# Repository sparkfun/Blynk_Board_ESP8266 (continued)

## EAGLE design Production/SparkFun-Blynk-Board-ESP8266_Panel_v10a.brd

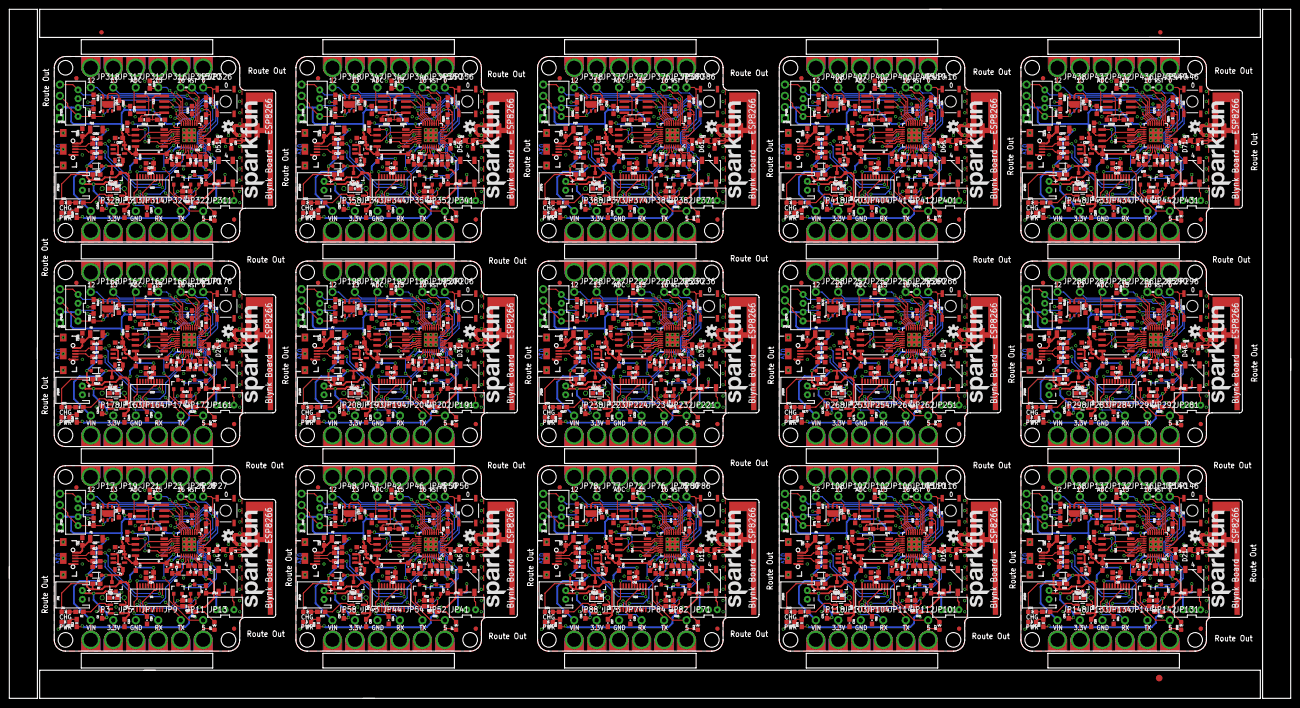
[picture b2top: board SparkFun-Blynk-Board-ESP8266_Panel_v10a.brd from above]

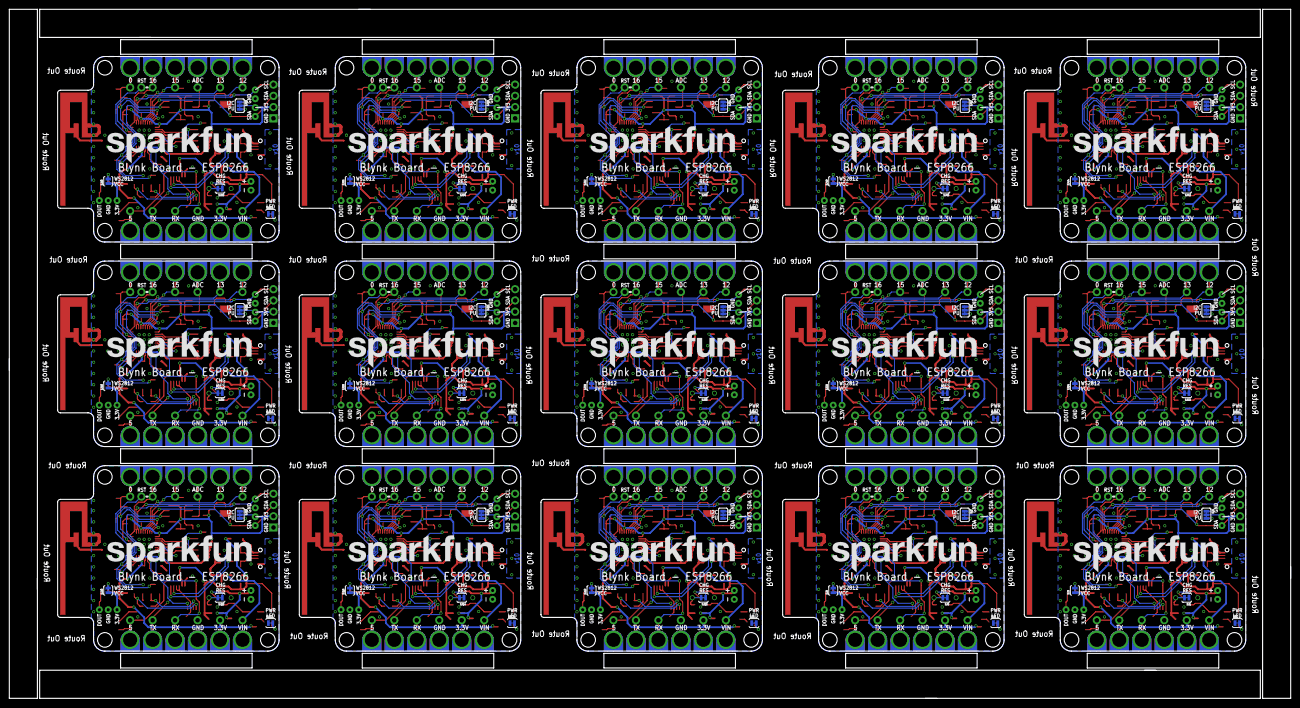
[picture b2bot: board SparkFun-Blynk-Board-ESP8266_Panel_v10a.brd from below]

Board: 2 copper layers, 289.6 x 155.7 mm, 1548 parts (75 on the bottom side), 840 nets.

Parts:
C1, C20, C39, C58, C77, C96, C115, C134, C153, C172, C191, C210, C229, C248, C267: 10uF; 0603-CAP
C2, C5, C9, C11, C14, C16, C17, C18, C21, C23, C24, C25, C29, C32, C33, C34, C40, C42, C43, C44, C48, C51, C52, C53, C59, C61, C62, C63, C67, C70, C71, C72, C78, C80, C81, C82, C86, C89, C90, C91, C97, C99, C100, C101, C105, C108, C109, C110, C116, C118, C119, C120, C124, C127, C128, C129, C135, C137, C138, C139, C143, C146, C147, C148, C154, C156, C157, C158, C162, C165, C166, C167, C173, C175, C176, C177, C181, C184, C185, C186, C192, C194, C195, C196, C200, C203, C204, C205, C211, C213, C214, C215, C219, C222, C223, C224, C230, C232, C233, C234, C238, C241, C242, C243, C249, C251, C252, C253, C257, C260, C261, C262, C268, C270, C271, C272, C276, C279, C280, C281: 0.1uF; 0603-CAP
C3, C4, C26, C27, C45, C46, C64, C65, C83, C84, C102, C103, C121, C122, C140, C141, C159, C160, C178, C179, C197, C198, C216, C217, C235, C236, C254, C255, C273, C274: 10pF; 0603-CAP
C6, C15, C19, C31, C37, C38, C50, C56, C57, C69, C75, C76, C88, C94, C95, C107, C113, C114, C126, C132, C133, C145, C151, C152, C164, C170, C171, C183, C189, C190, C202, C208, C209, C221, C227, C228, C240, C246, C247, C259, C265, C266, C278, C284, C285: 4.7uF; 0603-CAP
C7, C35, C54, C73, C92, C111, C130, C149, C168, C187, C206, C225, C244, C263, C282: 1.0uF; 0805-CAP
C8, C28, C47, C66, C85, C104, C123, C142, C161, C180, C199, C218, C237, C256, C275: 5.6pF; 0603-CAP
C10, C36, C55, C74, C93, C112, C131, C150, C169, C188, C207, C226, C245, C264, C283: 2.2uF; 0603-CAP
C12, C13, C22, C30, C41, C49, C60, C68, C79, C87, C98, C106, C117, C125, C136, C144, C155, C163, C174, C182, C193, C201, C212, C220, C231, C239, C250, C258, C269, C277: 47pF; 0603-CAP
D1, D9, D14, D19, D24, D29, D34, D39, D44, D49, D54, D59, D64, D69, D74: Yellow; LED-0603
D2, D8, D13, D18, D23, D28, D33, D38, D43, D48, D53, D58, D63, D68, D73: BAT20J; SOD-323
D3, D7, D12, D17, D22, D27, D32, D37, D42, D47, D52, D57, D62, D67, D72: BLUE; LED-0603
D4, D6, D11, D16, D21, D26, D31, D36, D41, D46, D51, D56, D61, D66, D71: WS2812; WS2812B
D5, D10, D15, D20, D25, D30, D35, D40, D45, D50, D55, D60, D65, D70, D75: RED; LED-0603
E1, E2, E3, E4, E5, E6, E7, E8, E9, E10, E11, E12, E13, E14, E15: ANTENNATRACE; TRACE_ANTENNA_2.4GHZ_25.7MM
E$1: FIDUCIAL-1.5X3
E$7, E$8: FIDUCIAL-1X2
F1, F2, F3, F4, F5, F6, F7, F8, F9, F10, F11, F12, F13, F14, F15: 500mA; PTC-1206
FID1, FID2, FID3, FID4, FID5, FID6, FID7, FID8, FID9, FID10, FID11, FID12, FID13, FID14, FID15, FID16, FID17, FID18, FID19, FID20, FID21, FID22, FID23, FID24, FID25, FID26, FID27, FID28, FID29, FID30: FIDUCIAL1X2; FIDUCIAL-1X2
IC1, IC2, IC3, IC4, IC5, IC6, IC7, IC8, IC9, IC10, IC11, IC12, IC13, IC14, IC15: LMV358; SO08
JP1, JP49, JP79, JP109, JP139, JP169, JP199, JP229, JP259, JP289, JP319, JP349, JP379, JP409, JP439: LiPo; JST-2-PTH
JP2, JP4, JP6, JP8, JP10, JP12, JP16, JP18, JP20, JP22, JP24, JP26, JP32, JP33, JP34, JP35, JP36, JP37, JP38, JP39, JP51, JP53, JP55, JP57, JP62, JP63, JP64, JP65, JP66, JP67, JP68, JP69, JP81, JP83, JP85, JP87, JP92, JP93, JP94, JP95, JP96, JP97, JP98, JP99, JP111, JP113, JP115, JP117, JP122, JP123, JP124, JP125, JP126, JP127, JP128, JP129, JP141, JP143, JP145, JP147, JP152, JP153, JP154, JP155, JP156, JP157, JP158, JP159, JP171, JP173, JP175, JP177, JP182, JP183, JP184, JP185, JP186, JP187, JP188, JP189, JP201, JP203, JP205, JP207, JP212, JP213, JP214, JP215, JP216, JP217, JP218, JP219, JP231, JP233, JP235, JP237, JP242, JP243, JP244, JP245, JP246, JP247, JP248, JP249, JP261, JP263, JP265, JP267, JP272, JP273, JP274, JP275, JP276, JP277, JP278, JP279, JP291, JP293, JP295, JP297, JP302, JP303, JP304, JP305, JP306, JP307, JP308, JP309, JP321, JP323, JP325, JP327, JP332, JP333, JP334, JP335, JP336, JP337, JP338, JP339, JP351, JP353, JP355, JP357, JP362, JP363, JP364, JP365, JP366, JP367, JP368, JP369, JP381, JP383, JP385, JP387, JP392, JP393, JP394, JP395, JP396, JP397, JP398, JP399, JP411, JP413, JP415, JP417, JP422, JP423, JP424, JP425, JP426, JP427, JP428, JP429, JP441, JP443, JP445, JP447: 1X01_ALLIGATOR_3MM_HALF
JP3, JP5, JP7, JP9, JP11, JP13, JP17, JP19, JP21, JP23, JP25, JP27, JP28, JP41, JP42, JP43, JP44, JP45, JP46, JP47, JP48, JP50, JP52, JP54, JP56, JP58, JP71, JP72, JP73, JP74, JP75, JP76, JP77, JP78, JP80, JP82, JP84, JP86, JP88, JP101, JP102, JP103, JP104, JP105, JP106, JP107, JP108, JP110, JP112, JP114, JP116, JP118, JP131, JP132, JP133, JP134, JP135, JP136, JP137, JP138, JP140, JP142, JP144, JP146, JP148, JP161, JP162, JP163, JP164, JP165, JP166, JP167, JP168, JP170, JP172, JP174, JP176, JP178, JP191, JP192, JP193, JP194, JP195, JP196, JP197, JP198, JP200, JP202, JP204, JP206, JP208, JP221, JP222, JP223, JP224, JP225, JP226, JP227, JP228, JP230, JP232, JP234, JP236, JP238, JP251, JP252, JP253, JP254, JP255, JP256, JP257, JP258, JP260, JP262, JP264, JP266, JP268, JP281, JP282, JP283, JP284, JP285, JP286, JP287, JP288, JP290, JP292, JP294, JP296, JP298, JP311, JP312, JP313, JP314, JP315, JP316, JP317, JP318, JP320, JP322, JP324, JP326, JP328, JP341, JP342, JP343, JP344, JP345, JP346, JP347, JP348, JP350, JP352, JP354, JP356, JP358, JP371, JP372, JP373, JP374, JP375, JP376, JP377, JP378, JP380, JP382, JP384, JP386, JP388, JP401, JP402, JP403, JP404, JP405, JP406, JP407, JP408, JP410, JP412, JP414, JP416, JP418, JP431, JP432, JP433, JP434, JP435, JP436, JP437, JP438, JP440, JP442, JP444, JP446, JP448: 1X01_NO_SILK
JP14, JP40, JP70, JP100, JP130, JP160, JP190, JP220, JP250, JP280, JP310, JP340, JP370, JP400, JP430: JST-3-PTH-VERT
JP15, JP31, JP61, JP91, JP121, JP151, JP181, JP211, JP241, JP271, JP301, JP331, JP361, JP391, JP421: USB-B-MICRO-SMD_V03
JP29, JP60, JP90, JP120, JP150, JP180, JP210, JP240, JP270, JP300, JP330, JP360, JP390, JP420, JP450: JST-4-PTH-VERT
JP30, JP59, JP89, JP119, JP149, JP179, JP209, JP239, JP269, JP299, JP329, JP359, JP389, JP419, JP449: 1X04_NO_SILK
L1, L2, L3, L4, L5, L6, L7, L8, L9, L10, L11, L12, L13, L14, L15, L16, L17, L18, L19, L20, L21, L22, L23, L24, L25, L26, L27, L28, L29, L30: DNP; 0603
LOGO1, LOGO4, LOGO7, LOGO10, LOGO13, LOGO16, LOGO19, LOGO22, LOGO25, LOGO28, LOGO31, LOGO34, LOGO37, LOGO40, LOGO43: SFE_LOGO_NAME.2_INCH; SFE_LOGO_NAME_.2
LOGO2, LOGO5, LOGO8, LOGO11, LOGO14, LOGO17, LOGO20, LOGO23, LOGO26, LOGO29, LOGO32, LOGO35, LOGO38, LOGO41, LOGO44: OSHW-LOGOS; OSHW-LOGO-S
LOGO3, LOGO6, LOGO9, LOGO12, LOGO15, LOGO18, LOGO21, LOGO24, LOGO27, LOGO30, LOGO33, LOGO36, LOGO39, LOGO42, LOGO45: SFE_LOGO_NAME.3_INCH; SFE_LOGO_NAME_.3
Q1, Q6, Q9, Q12, Q15, Q18, Q21, Q24, Q27, Q30, Q33, Q36, Q39, Q42, Q45: 2.5A/30V; SOT23-3
Q2, Q3, Q4, Q5, Q7, Q8, Q10, Q11, Q13, Q14, Q16, Q17, Q19, Q20, Q22, Q23, Q25, Q26, Q28, Q29, Q31, Q32, Q34, Q35, Q37, Q38, Q40, Q41, Q43, Q44: MMBT2222A; SOT23-3@1
R1, R21, R41, R61, R81, R101, R121, R141, R161, R181, R201, R221, R241, R261, R281: 12k; 0603-RES
R2, R12, R37, R38, R57, R58, R77, R78, R97, R98, R117, R118, R137, R138, R157, R158, R177, R178, R197, R198, R217, R218, R237, R238, R257, R258, R277, R278, R297, R298: 1K; 0603-RES
R3, R33, R53, R73, R93, R113, R133, R153, R173, R193, R213, R233, R253, R273, R293: 22K; 0603-RES
R4, R34, R54, R74, R94, R114, R134, R154, R174, R194, R214, R234, R254, R274, R294: 10K; 0603-RES
R5, R40, R60, R80, R100, R120, R140, R160, R180, R200, R220, R240, R260, R280, R300: DNP; 1/6W-RES
R6, R39, R59, R79, R99, R119, R139, R159, R179, R199, R219, R239, R259, R279, R299: 2.0k; 0603-RES
R7, R8, R10, R17, R18, R19, R20, R22, R23, R24, R25, R27, R30, R36, R42, R43, R44, R45, R47, R50, R56, R62, R63, R64, R65, R67, R70, R76, R82, R83, R84, R85, R87, R90, R96, R102, R103, R104, R105, R107, R110, R116, R122, R123, R124, R125, R127, R130, R136, R142, R143, R144, R145, R147, R150, R156, R162, R163, R164, R165, R167, R170, R176, R182, R183, R184, R185, R187, R190, R196, R202, R203, R204, R205, R207, R210, R216, R222, R223, R224, R225, R227, R230, R236, R242, R243, R244, R245, R247, R250, R256, R262, R263, R264, R265, R267, R270, R276, R282, R283, R284, R285, R287, R290, R296: 10K; 0603-RES@1
R9, R26, R46, R66, R86, R106, R126, R146, R166, R186, R206, R226, R246, R266, R286: 200; 0603-RES
R11, R35, R55, R75, R95, R115, R135, R155, R175, R195, R215, R235, R255, R275, R295: 330; 0603-RES
R13, R14, R28, R29, R48, R49, R68, R69, R88, R89, R108, R109, R128, R129, R148, R149, R168, R169, R188, R189, R208, R209, R228, R229, R248, R249, R268, R269, R288, R289: 27; 0603-RES
R15, R16, R31, R32, R51, R52, R71, R72, R91, R92, R111, R112, R131, R132, R151, R152, R171, R172, R191, R192, R211, R212, R231, R232, R251, R252, R271, R272, R291, R292: 4.7K; 0603-RES
S1, S2, S3, S4, S5, S6, S7, S8, S9, S10, S11, S12, S13, S14, S15: TACTILE-SWITCH-SMD
SJ1, SJ6, SJ10, SJ14, SJ18, SJ22, SJ26, SJ30, SJ34, SJ38, SJ42, SJ46, SJ50, SJ54, SJ58: PAD-JUMPER-2-NC_BY_TRACE_YES_SILK
SJ2, SJ5, SJ9, SJ13, SJ17, SJ21, SJ25, SJ29, SJ33, SJ37, SJ41, SJ45, SJ49, SJ53, SJ57: PWRLED; PAD-JUMPER-2-NC_BY_TRACE_YES_SILK
SJ3, SJ8, SJ12, SJ16, SJ20, SJ24, SJ28, SJ32, SJ36, SJ40, SJ44, SJ48, SJ52, SJ56, SJ60: WS2812-VCC; PAD-JUMPER-2-NC_BY_TRACE_YES_SILK
SJ4, SJ7, SJ11, SJ15, SJ19, SJ23, SJ27, SJ31, SJ35, SJ39, SJ43, SJ47, SJ51, SJ55, SJ59: PAD-JUMPER-3-3OF3_NC_BY_TRACE_YES_SILK_FULL_BOX
STANDOFF1, STANDOFF2, STANDOFF3, STANDOFF4, STANDOFF5, STANDOFF6, STANDOFF7, STANDOFF8, STANDOFF9, STANDOFF10, STANDOFF11, STANDOFF12, STANDOFF13, STANDOFF14, STANDOFF15, STANDOFF16, STANDOFF17, STANDOFF18, STANDOFF19, STANDOFF20, STANDOFF21, STANDOFF22, STANDOFF23, STANDOFF24, STANDOFF25, STANDOFF26, STANDOFF27, STANDOFF28, STANDOFF29, STANDOFF30, STANDOFF31, STANDOFF32, STANDOFF33, STANDOFF34, STANDOFF35, STANDOFF36, STANDOFF37, STANDOFF38, STANDOFF39, STANDOFF40, STANDOFF41, STANDOFF42, STANDOFF43, STANDOFF44, STANDOFF45, STANDOFF46, STANDOFF47, STANDOFF48, STANDOFF49, STANDOFF50, STANDOFF51, STANDOFF52, STANDOFF53, STANDOFF54, STANDOFF55, STANDOFF56, STANDOFF57, STANDOFF58, STANDOFF59, STANDOFF60: STAND-OFF
U1, U11, U17, U23, U29, U35, U41, U47, U53, U59, U65, U71, U77, U83, U89: MCP73831; SOT23-5
U2, U7, U13, U19, U25, U31, U37, U43, U49, U55, U61, U67, U73, U79, U85: ESP8266; QFN32
U3, U12, U18, U24, U30, U36, U42, U48, U54, U60, U66, U72, U78, U84, U90: AP2112K-3.3V; SOT23-5
U4, U9, U15, U21, U27, U33, U39, U45, U51, U57, U63, U69, U75, U81, U87: FT231XS-U; SSOP20_L
U5, U8, U14, U20, U26, U32, U38, U44, U50, U56, U62, U68, U74, U80, U86: W25Q32FVSS; SOIC-8
U6, U10, U16, U22, U28, U34, U40, U46, U52, U58, U64, U70, U76, U82, U88: SI7021
Y1, Y2, Y3, Y4, Y5, Y6, Y7, Y8, Y9, Y10, Y11, Y12, Y13, Y14, Y15: 26MHz; CRYSTAL-SMD-3.2X2.5

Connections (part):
0/BUTTON: JP26.1@2, JP27.1, Q3.3, R19.1, S1.1, S1.2, U2.15
0/BUTTON1: JP55.1@2, JP56.1, Q5.3, R23.1, S2.1, S2.2, U7.15
0/BUTTON2: JP85.1@2, JP86.1, Q8.3, R43.1, S3.1, S3.2, U13.15
0/BUTTON3: JP115.1@2, JP116.1, Q11.3, R63.1, S4.1, S4.2, U19.15
0/BUTTON4: JP145.1@2, JP146.1, Q14.3, R83.1, S5.1, S5.2, U25.15
0/BUTTON5: JP175.1@2, JP176.1, Q17.3, R103.1, S6.1, S6.2, U31.15
0/BUTTON6: JP205.1@2, JP206.1, Q20.3, R123.1, S7.1, S7.2, U37.15
0/BUTTON7: JP235.1@2, JP236.1, Q23.3, R143.1, S8.1, S8.2, U43.15
0/BUTTON8: JP265.1@2, JP266.1, Q26.3, R163.1, S9.1, S9.2, U49.15
0/BUTTON9: JP295.1@2, JP296.1, Q29.3, R183.1, S10.1, S10.2, U55.15
0/BUTTON10: JP325.1@2, JP326.1, Q32.3, R203.1, S11.1, S11.2, U61.15
0/BUTTON11: JP355.1@2, JP356.1, Q35.3, R223.1, S12.1, S12.2, U67.15
0/BUTTON12: JP385.1@2, JP386.1, Q38.3, R243.1, S13.1, S13.2, U73.15
0/BUTTON13: JP415.1@2, JP416.1, Q41.3, R263.1, S14.1, S14.2, U79.15
0/BUTTON14: JP445.1@2, JP446.1, Q44.3, R283.1, S15.1, S15.2, U85.15
2/SDA: JP29.1, JP30.3, R15.1, U2.14, U6.DATA
2/SDA1: JP59.3, JP60.1, R31.1, U7.14, U10.DATA
2/SDA2: JP89.3, JP90.1, R51.1, U13.14, U16.DATA
2/SDA3: JP119.3, JP120.1, R71.1, U19.14, U22.DATA
2/SDA4: JP149.3, JP150.1, R91.1, U25.14, U28.DATA
2/SDA5: JP179.3, JP180.1, R111.1, U31.14, U34.DATA
2/SDA6: JP209.3, JP210.1, R131.1, U37.14, U40.DATA
2/SDA7: JP239.3, JP240.1, R151.1, U43.14, U46.DATA
2/SDA8: JP269.3, JP270.1, R171.1, U49.14, U52.DATA
2/SDA9: JP299.3, JP300.1, R191.1, U55.14, U58.DATA
2/SDA10: JP329.3, JP330.1, R211.1, U61.14, U64.DATA
2/SDA11: JP359.3, JP360.1, R231.1, U67.14, U70.DATA
2/SDA12: JP389.3, JP390.1, R251.1, U73.14, U76.DATA
2/SDA13: JP419.3, JP420.1, R271.1, U79.14, U82.DATA
2/SDA14: JP449.3, JP450.1, R291.1, U85.14, U88.DATA
3.3V_F: C16.1, U4.3, U4.13, U4.14
3.3V_F1: C24.1, U9.3, U9.13, U9.14
3.3V_F2: C43.1, U15.3, U15.13, U15.14
3.3V_F3: C62.1, U21.3, U21.13, U21.14
3.3V_F4: C81.1, U27.3, U27.13, U27.14
3.3V_F5: C100.1, U33.3, U33.13, U33.14
3.3V_F6: C119.1, U39.3, U39.13, U39.14
3.3V_F7: C138.1, U45.3, U45.13, U45.14
3.3V_F8: C157.1, U51.3, U51.13, U51.14
3.3V_F9: C176.1, U57.3, U57.13, U57.14
3.3V_F10: C195.1, U63.3, U63.13, U63.14
3.3V_F11: C214.1, U69.3, U69.13, U69.14
3.3V_F12: C233.1, U75.3, U75.13, U75.14
3.3V_F13: C252.1, U81.3, U81.13, U81.14
3.3V_F14: C271.1, U87.3, U87.13, U87.14
4/WS1: D6.4, U7.16
4/WS2: D11.4, U13.16
4/WS3: D16.4, U19.16
4/WS4: D21.4, U25.16
4/WS5: D26.4, U31.16
4/WS6: D31.4, U37.16
4/WS7: D36.4, U43.16
4/WS8: D41.4, U49.16
4/WS9: D46.4, U55.16
4/WS10: D51.4, U61.16
4/WS11: D56.4, U67.16
4/WS12: D61.4, U73.16
4/WS13: D66.4, U79.16
4/WS14: D71.4, U85.16
4/WS2812: D4.4, U2.16
14/SCL: JP29.4, JP30.4, R16.1, U2.9, U6.SCK
14/SCL1: JP59.4, JP60.4, R32.1, U7.9, U10.SCK
14/SCL2: JP89.4, JP90.4, R52.1, U13.9, U16.SCK
14/SCL3: JP119.4, JP120.4, R72.1, U19.9, U22.SCK
14/SCL4: JP149.4, JP150.4, R92.1, U25.9, U28.SCK
14/SCL5: JP179.4, JP180.4, R112.1, U31.9, U34.SCK
14/SCL6: JP209.4, JP210.4, R132.1, U37.9, U40.SCK
14/SCL7: JP239.4, JP240.4, R152.1, U43.9, U46.SCK
14/SCL8: JP269.4, JP270.4, R172.1, U49.9, U52.SCK
14/SCL9: JP299.4, JP300.4, R192.1, U55.9, U58.SCK
14/SCL10: JP329.4, JP330.4, R212.1, U61.9, U64.SCK
14/SCL11: JP359.4, JP360.4, R232.1, U67.9, U70.SCK
14/SCL12: JP389.4, JP390.4, R252.1, U73.9, U76.SCK
14/SCL13: JP419.4, JP420.4, R272.1, U79.9, U82.SCK
14/SCL14: JP449.4, JP450.4, R292.1, U85.9, U88.SCK
ADC: IC1.6, IC1.7, U2.6
ADC1: IC2.6, IC2.7, U7.6
ADC2: IC3.6, IC3.7, U13.6
ADC3: IC4.6, IC4.7, U19.6
ADC4: IC5.6, IC5.7, U25.6
ADC5: IC6.6, IC6.7, U31.6
ADC6: IC7.6, IC7.7, U37.6
ADC7: IC8.6, IC8.7, U43.6
ADC8: IC9.6, IC9.7, U49.6
ADC9: IC10.6, IC10.7, U55.6
ADC10: IC11.6, IC11.7, U61.6
ADC11: IC12.6, IC12.7, U67.6
ADC12: IC13.6, IC13.7, U73.6
ADC13: IC14.6, IC14.7, U79.6
ADC14: IC15.6, IC15.7, U85.6
ADC-IN: IC1.3, JP20.1@2, JP21.1
ADC-IN1: IC2.3, JP37.1@2, JP42.1
ADC-IN2: IC3.3, JP67.1@2, JP72.1
ADC-IN3: IC4.3, JP97.1@2, JP102.1
ADC-IN4: IC5.3, JP127.1@2, JP132.1
ADC-IN5: IC6.3, JP157.1@2, JP162.1
ADC-IN6: IC7.3, JP187.1@2, JP192.1
ADC-IN7: IC8.3, JP217.1@2, JP222.1
ADC-IN8: IC9.3, JP247.1@2, JP252.1
ADC-IN9: IC10.3, JP277.1@2, JP282.1
ADC-IN10: IC11.3, JP307.1@2, JP312.1
ADC-IN11: IC12.3, JP337.1@2, JP342.1
ADC-IN12: IC13.3, JP367.1@2, JP372.1
ADC-IN13: IC14.3, JP397.1@2, JP402.1
ADC-IN14: IC15.3, JP427.1@2, JP432.1
CHIP_EN: R8.1, U2.7
CHIP_EN1: R25.1, U7.7
CHIP_EN2: R45.1, U13.7
CHIP_EN3: R65.1, U19.7
CHIP_EN4: R85.1, U25.7
CHIP_EN5: R105.1, U31.7
CHIP_EN6: R125.1, U37.7
CHIP_EN7: R145.1, U43.7
CHIP_EN8: R165.1, U49.7
CHIP_EN9: R185.1, U55.7
CHIP_EN10: R205.1, U61.7
CHIP_EN11: R225.1, U67.7
CHIP_EN12: R245.1, U73.7
CHIP_EN13: R265.1, U79.7
CHIP_EN14: R285.1, U85.7
D+: C13.1, JP15.D+, R14.1
D+1: C22.1, JP31.D+, R29.1
D+2: C41.1, JP61.D+, R49.1
D+3: C60.1, JP91.D+, R69.1
D+4: C79.1, JP121.D+, R89.1
D+5: C98.1, JP151.D+, R109.1
D+6: C117.1, JP181.D+, R129.1
D+7: C136.1, JP211.D+, R149.1
D+8: C155.1, JP241.D+, R169.1
D+9: C174.1, JP271.D+, R189.1
D+10: C193.1, JP301.D+, R209.1
D+11: C212.1, JP331.D+, R229.1
D+12: C231.1, JP361.D+, R249.1
D+13: C250.1, JP391.D+, R269.1
D+14: C269.1, JP421.D+, R289.1
D-: C12.1, JP15.D-, R13.1
D-1: C30.1, JP31.D-, R28.1
D-2: C49.1, JP61.D-, R48.1
D-3: C68.1, JP91.D-, R68.1
D-4: C87.1, JP121.D-, R88.1
D-5: C106.1, JP151.D-, R108.1
D-6: C125.1, JP181.D-, R128.1
D-7: C144.1, JP211.D-, R148.1
D-8: C163.1, JP241.D-, R168.1
D-9: C182.1, JP271.D-, R188.1
D-10: C201.1, JP301.D-, R208.1
D-11: C220.1, JP331.D-, R228.1
D-12: C239.1, JP361.D-, R248.1
D-13: C258.1, JP391.D-, R268.1
D-14: C277.1, JP421.D-, R288.1
DTR: Q3.2, R17.1, U4.1
DTR1: Q5.2, R30.1, U9.1
DTR2: Q8.2, R50.1, U15.1
DTR3: Q11.2, R70.1, U21.1
DTR4: Q14.2, R90.1, U27.1
DTR5: Q17.2, R110.1, U33.1
DTR6: Q20.2, R130.1, U39.1
DTR7: Q23.2, R150.1, U45.1
DTR8: Q26.2, R170.1, U51.1
DTR9: Q29.2, R190.1, U57.1
DTR10: Q32.2, R210.1, U63.1
DTR11: Q35.2, R230.1, U69.1
DTR12: Q38.2, R250.1, U75.1
DTR13: Q41.2, R270.1, U81.1
DTR14: Q44.2, R290.1, U87.1
GND: C1.2, C2.2, C3.1, C4.1, C5.2, C6.2, C7.2, C9.2, C10.2, C11.2, C12.2, C13.2, C14.2, C15.2, C16.2, C17.2, C18.2, C19.2, D4.3, E1.GND, E1.GND2, IC1.4, JP1.1, JP6.1@2, JP7.1, JP14.2, JP15.GND, JP29.3, JP30.1, L1.2, L2.2, R1.1, R4.1, R5.1, R6.1, R7.1, R11.2, R20.1, S1.3, S1.4, SJ2.1, U1.2, U2.EP, U3.2, U4.6, U4.16, U5.4, U6.GND, Y1.2, Y1.4
GND1: C20.2, C21.2, C22.2, C23.2, C24.2, C25.2, C26.1, C27.1, C29.2, C30.2, C31.2, C32.2, C33.2, C34.2, C35.2, C36.2, C37.2, C38.2, D6.3, E2.GND, E2.GND2, IC2.4, JP31.GND, JP39.1@2, JP40.2, JP44.1, JP49.1, JP59.1, JP60.3, L3.2, L4.2, R21.1, R24.1, R34.1, R35.2, R36.1, R39.1, R40.1, S2.3, S2.4, SJ5.1, U7.EP, U8.4, U9.6, U9.16, U10.GND, U11.2, U12.2, Y2.2, Y2.4
GND2: C39.2, C40.2, C41.2, C42.2, C43.2, C44.2, C45.1, C46.1, C48.2, C49.2, C50.2, C51.2, C52.2, C53.2, C54.2, C55.2, C56.2, C57.2, D11.3, E3.GND, E3.GND2, IC3.4, JP61.GND, JP69.1@2, JP70.2, JP74.1, JP79.1, JP89.1, JP90.3, L5.2, L6.2, R41.1, R44.1, R54.1, R55.2, R56.1, R59.1, R60.1, S3.3, S3.4, SJ9.1, U13.EP, U14.4, U15.6, U15.16, U16.GND, U17.2, U18.2, Y3.2, Y3.4
GND3: C58.2, C59.2, C60.2, C61.2, C62.2, C63.2, C64.1, C65.1, C67.2, C68.2, C69.2, C70.2, C71.2, C72.2, C73.2, C74.2, C75.2, C76.2, D16.3, E4.GND, E4.GND2, IC4.4, JP91.GND, JP99.1@2, JP100.2, JP104.1, JP109.1, JP119.1, JP120.3, L7.2, L8.2, R61.1, R64.1, R74.1, R75.2, R76.1, R79.1, R80.1, S4.3, S4.4, SJ13.1, U19.EP, U20.4, U21.6, U21.16, U22.GND, U23.2, U24.2, Y4.2, Y4.4
GND4: C77.2, C78.2, C79.2, C80.2, C81.2, C82.2, C83.1, C84.1, C86.2, C87.2, C88.2, C89.2, C90.2, C91.2, C92.2, C93.2, C94.2, C95.2, D21.3, E5.GND, E5.GND2, IC5.4, JP121.GND, JP129.1@2, JP130.2, JP134.1, JP139.1, JP149.1, JP150.3, L9.2, L10.2, R81.1, R84.1, R94.1, R95.2, R96.1, R99.1, R100.1, S5.3, S5.4, SJ17.1, U25.EP, U26.4, U27.6, U27.16, U28.GND, U29.2, U30.2, Y5.2, Y5.4
GND5: C96.2, C97.2, C98.2, C99.2, C100.2, C101.2, C102.1, C103.1, C105.2, C106.2, C107.2, C108.2, C109.2, C110.2, C111.2, C112.2, C113.2, C114.2, D26.3, E6.GND, E6.GND2, IC6.4, JP151.GND, JP159.1@2, JP160.2, JP164.1, JP169.1, JP179.1, JP180.3, L11.2, L12.2, R101.1, R104.1, R114.1, R115.2, R116.1, R119.1, R120.1, S6.3, S6.4, SJ21.1, U31.EP, U32.4, U33.6, U33.16, U34.GND, U35.2, U36.2, Y6.2, Y6.4
GND6: C115.2, C116.2, C117.2, C118.2, C119.2, C120.2, C121.1, C122.1, C124.2, C125.2, C126.2, C127.2, C128.2, C129.2, C130.2, C131.2, C132.2, C133.2, D31.3, E7.GND, E7.GND2, IC7.4, JP181.GND, JP189.1@2, JP190.2, JP194.1, JP199.1, JP209.1, JP210.3, L13.2, L14.2, R121.1, R124.1, R134.1, R135.2, R136.1, R139.1, R140.1, S7.3, S7.4, SJ25.1, U37.EP, U38.4, U39.6, U39.16, U40.GND, U41.2, U42.2, Y7.2, Y7.4
GND7: C134.2, C135.2, C136.2, C137.2, C138.2, C139.2, C140.1, C141.1, C143.2, C144.2, C145.2, C146.2, C147.2, C148.2, C149.2, C150.2, C151.2, C152.2, D36.3, E8.GND, E8.GND2, IC8.4, JP211.GND, JP219.1@2, JP220.2, JP224.1, JP229.1, JP239.1, JP240.3, L15.2, L16.2, R141.1, R144.1, R154.1, R155.2, R156.1, R159.1, R160.1, S8.3, S8.4, SJ29.1, U43.EP, U44.4, U45.6, U45.16, U46.GND, U47.2, U48.2, Y8.2, Y8.4
GND8: C153.2, C154.2, C155.2, C156.2, C157.2, C158.2, C159.1, C160.1, C162.2, C163.2, C164.2, C165.2, C166.2, C167.2, C168.2, C169.2, C170.2, C171.2, D41.3, E9.GND, E9.GND2, IC9.4, JP241.GND, JP249.1@2, JP250.2, JP254.1, JP259.1, JP269.1, JP270.3, L17.2, L18.2, R161.1, R164.1, R174.1, R175.2, R176.1, R179.1, R180.1, S9.3, S9.4, SJ33.1, U49.EP, U50.4, U51.6, U51.16, U52.GND, U53.2, U54.2, Y9.2, Y9.4
GND9: C172.2, C173.2, C174.2, C175.2, C176.2, C177.2, C178.1, C179.1, C181.2, C182.2, C183.2, C184.2, C185.2, C186.2, C187.2, C188.2, C189.2, C190.2, D46.3, E10.GND, E10.GND2, IC10.4, JP271.GND, JP279.1@2, JP280.2, JP284.1, JP289.1, JP299.1, JP300.3, L19.2, L20.2, R181.1, R184.1, R194.1, R195.2, R196.1, R199.1, R200.1, S10.3, S10.4, SJ37.1, U55.EP, U56.4, U57.6, U57.16, U58.GND, U59.2, U60.2, Y10.2, Y10.4
GND10: C191.2, C192.2, C193.2, C194.2, C195.2, C196.2, C197.1, C198.1, C200.2, C201.2, C202.2, C203.2, C204.2, C205.2, C206.2, C207.2, C208.2, C209.2, D51.3, E11.GND, E11.GND2, IC11.4, JP301.GND, JP309.1@2, JP310.2, JP314.1, JP319.1, JP329.1, JP330.3, L21.2, L22.2, R201.1, R204.1, R214.1, R215.2, R216.1, R219.1, R220.1, S11.3, S11.4, SJ41.1, U61.EP, U62.4, U63.6, U63.16, U64.GND, U65.2, U66.2, Y11.2, Y11.4
GND11: C210.2, C211.2, C212.2, C213.2, C214.2, C215.2, C216.1, C217.1, C219.2, C220.2, C221.2, C222.2, C223.2, C224.2, C225.2, C226.2, C227.2, C228.2, D56.3, E12.GND, E12.GND2, IC12.4, JP331.GND, JP339.1@2, JP340.2, JP344.1, JP349.1, JP359.1, JP360.3, L23.2, L24.2, R221.1, R224.1, R234.1, R235.2, R236.1, R239.1, R240.1, S12.3, S12.4, SJ45.1, U67.EP, U68.4, U69.6, U69.16, U70.GND, U71.2, U72.2, Y12.2, Y12.4
GND12: C229.2, C230.2, C231.2, C232.2, C233.2, C234.2, C235.1, C236.1, C238.2, C239.2, C240.2, C241.2, C242.2, C243.2, C244.2, C245.2, C246.2, C247.2, D61.3, E13.GND, E13.GND2, IC13.4, JP361.GND, JP369.1@2, JP370.2, JP374.1, JP379.1, JP389.1, JP390.3, L25.2, L26.2, R241.1, R244.1, R254.1, R255.2, R256.1, R259.1, R260.1, S13.3, S13.4, SJ49.1, U73.EP, U74.4, U75.6, U75.16, U76.GND, U77.2, U78.2, Y13.2, Y13.4
GND13: C248.2, C249.2, C250.2, C251.2, C252.2, C253.2, C254.1, C255.1, C257.2, C258.2, C259.2, C260.2, C261.2, C262.2, C263.2, C264.2, C265.2, C266.2, D66.3, E14.GND, E14.GND2, IC14.4, JP391.GND, JP399.1@2, JP400.2, JP404.1, JP409.1, JP419.1, JP420.3, L27.2, L28.2, R261.1, R264.1, R274.1, R275.2, R276.1, R279.1, R280.1, S14.3, S14.4, SJ53.1, U79.EP, U80.4, U81.6, U81.16, U82.GND, U83.2, U84.2, Y14.2, Y14.4
GND14: C267.2, C268.2, C269.2, C270.2, C271.2, C272.2, C273.1, C274.1, C276.2, C277.2, C278.2, C279.2, C280.2, C281.2, C282.2, C283.2, C284.2, C285.2, D71.3, E15.GND, E15.GND2, IC15.4, JP421.GND, JP429.1@2, JP430.2, JP434.1, JP439.1, JP449.1, JP450.3, L29.2, L30.2, R281.1, R284.1, R294.1, R295.2, R296.1, R299.1, R300.1, S15.3, S15.4, SJ57.1, U85.EP, U86.4, U87.6, U87.16, U88.GND, U89.2, U90.2, Y15.2, Y15.4
GPIO1: D7.A, JP36.1@2, JP41.1, U7.24
GPIO2: JP35.1@2, JP45.1, U7.8
GPIO3: JP34.1@2, JP46.1, R24.2, U7.13
GPIO4: JP33.1@2, JP47.1, U7.12
GPIO5: D3.A, JP12.1@2, JP13.1, U2.24
GPIO6: JP32.1@2, JP48.1, U7.10
GPIO7: D12.A, JP66.1@2, JP71.1, U13.24
GPIO8: JP65.1@2, JP75.1, U13.8
GPIO9: JP64.1@2, JP76.1, R44.2, U13.13
GPIO10: JP63.1@2, JP77.1, U13.12
GPIO11: JP62.1@2, JP78.1, U13.10
GPIO12: JP16.1@2, JP17.1, U2.10
GPIO13: JP18.1@2, JP19.1, U2.12
GPIO14: D17.A, JP96.1@2, JP101.1, U19.24
GPIO15: JP22.1@2, JP23.1, R20.2, U2.13
GPIO16: JP24.1@2, JP25.1, U2.8
GPIO17: JP95.1@2, JP105.1, U19.8
GPIO18: JP94.1@2, JP106.1, R64.2, U19.13
GPIO19: JP93.1@2, JP107.1, U19.12
GPIO20: JP92.1@2, JP108.1, U19.10
GPIO21: D22.A, JP126.1@2, JP131.1, U25.24
GPIO22: JP125.1@2, JP135.1, U25.8
GPIO23: JP124.1@2, JP136.1, R84.2, U25.13
GPIO24: JP123.1@2, JP137.1, U25.12
GPIO25: JP122.1@2, JP138.1, U25.10
GPIO26: D27.A, JP156.1@2, JP161.1, U31.24
GPIO27: JP155.1@2, JP165.1, U31.8
GPIO28: JP154.1@2, JP166.1, R104.2, U31.13
GPIO29: JP153.1@2, JP167.1, U31.12
GPIO30: JP152.1@2, JP168.1, U31.10
GPIO31: D32.A, JP186.1@2, JP191.1, U37.24
GPIO32: JP185.1@2, JP195.1, U37.8
GPIO33: JP184.1@2, JP196.1, R124.2, U37.13
GPIO34: JP183.1@2, JP197.1, U37.12
GPIO35: JP182.1@2, JP198.1, U37.10
GPIO36: D37.A, JP216.1@2, JP221.1, U43.24
GPIO37: JP215.1@2, JP225.1, U43.8
GPIO38: JP214.1@2, JP226.1, R144.2, U43.13
GPIO39: JP213.1@2, JP227.1, U43.12
GPIO40: JP212.1@2, JP228.1, U43.10
GPIO41: D42.A, JP246.1@2, JP251.1, U49.24
GPIO42: JP245.1@2, JP255.1, U49.8
GPIO43: JP244.1@2, JP256.1, R164.2, U49.13
GPIO44: JP243.1@2, JP257.1, U49.12
GPIO45: JP242.1@2, JP258.1, U49.10
GPIO46: D47.A, JP276.1@2, JP281.1, U55.24
GPIO47: JP275.1@2, JP285.1, U55.8
GPIO48: JP274.1@2, JP286.1, R184.2, U55.13
GPIO49: JP273.1@2, JP287.1, U55.12
GPIO50: JP272.1@2, JP288.1, U55.10
GPIO51: D52.A, JP306.1@2, JP311.1, U61.24
GPIO52: JP305.1@2, JP315.1, U61.8
GPIO53: JP304.1@2, JP316.1, R204.2, U61.13
GPIO54: JP303.1@2, JP317.1, U61.12
GPIO55: JP302.1@2, JP318.1, U61.10
GPIO56: D57.A, JP336.1@2, JP341.1, U67.24
GPIO57: JP335.1@2, JP345.1, U67.8
GPIO58: JP334.1@2, JP346.1, R224.2, U67.13
GPIO59: JP333.1@2, JP347.1, U67.12
GPIO60: JP332.1@2, JP348.1, U67.10
GPIO61: D62.A, JP366.1@2, JP371.1, U73.24
GPIO62: JP365.1@2, JP375.1, U73.8
GPIO63: JP364.1@2, JP376.1, R244.2, U73.13
GPIO64: JP363.1@2, JP377.1, U73.12
GPIO65: JP362.1@2, JP378.1, U73.10
GPIO66: D67.A, JP396.1@2, JP401.1, U79.24
GPIO67: JP395.1@2, JP405.1, U79.8
GPIO68: JP394.1@2, JP406.1, R264.2, U79.13
GPIO69: JP393.1@2, JP407.1, U79.12
GPIO70: JP392.1@2, JP408.1, U79.10
GPIO71: D72.A, JP426.1@2, JP431.1, U85.24
GPIO72: JP425.1@2, JP435.1, U85.8
GPIO73: JP424.1@2, JP436.1, R284.2, U85.13
GPIO74: JP423.1@2, JP437.1, U85.12
GPIO75: JP422.1@2, JP438.1, U85.10
LNA: C8.1, L1.1, U2.2
LNA1: C28.1, L3.1, U7.2
LNA2: C47.1, L5.1, U13.2
LNA3: C66.1, L7.1, U19.2
LNA4: C85.1, L9.1, U25.2
LNA5: C104.1, L11.1, U31.2
LNA6: C123.1, L13.1, U37.2
LNA7: C142.1, L15.1, U43.2
LNA8: C161.1, L17.1, U49.2
LNA9: C180.1, L19.1, U55.2
LNA10: C199.1, L21.1, U61.2
LNA11: C218.1, L23.1, U67.2
LNA12: C237.1, L25.1, U73.2
LNA13: C256.1, L27.1, U79.2
LNA14: C275.1, L29.1, U85.2
unnamed: R1.2, U2.31
unnamed: C4.2, U2.28, Y1.3
unnamed: C3.2, U2.27, Y1.1
unnamed: R13.2, U4.12
unnamed: D5.C, SJ2.2
unnamed: Q2.1, R17.2
unnamed: R14.2, U4.11
unnamed: D3.C, R11.1
unnamed: R2.1, U1.1
unnamed: D5.A, R12.2
unnamed: R15.2, SJ4.3
unnamed: Q3.1, R18.2
unnamed: R16.2, SJ4.1
unnamed: R5.2, SJ1.2, U1.5
unnamed: IC1.1, IC1.2, R3.2
unnamed: R6.2, SJ1.1
unnamed: D1.C, R2.2
unnamed: IC1.5, R3.1, R4.2
unnamed: JP14.1, SJ3.1
unnamed: R21.2, U7.31
unnamed: C27.2, U7.28, Y2.3
unnamed: C26.2, U7.27, Y2.1
unnamed: R28.2, U9.12
unnamed: R29.2, U9.11
unnamed: Q4.1, R30.2
unnamed: Q5.1, R22.2
unnamed: IC2.1, IC2.2, R33.2
unnamed: IC2.5, R33.1, R34.2
unnamed: D7.C, R35.1
unnamed: D9.C, R37.2
unnamed: R37.1, U11.1
unnamed: R40.2, SJ6.2, U11.5
unnamed: D10.C, SJ5.2
unnamed: D10.A, R38.2
unnamed: R31.2, SJ7.3
unnamed: R32.2, SJ7.1
unnamed: R39.2, SJ6.1
unnamed: JP40.1, SJ8.1
unnamed: R41.2, U13.31
unnamed: C46.2, U13.28, Y3.3
unnamed: C45.2, U13.27, Y3.1
unnamed: R48.2, U15.12
unnamed: R49.2, U15.11
unnamed: Q7.1, R50.2
unnamed: Q8.1, R42.2
unnamed: IC3.1, IC3.2, R53.2
unnamed: IC3.5, R53.1, R54.2
unnamed: D12.C, R55.1
unnamed: D14.C, R57.2
unnamed: R57.1, U17.1
unnamed: R60.2, SJ10.2, U17.5
unnamed: D15.C, SJ9.2
unnamed: D15.A, R58.2
unnamed: R51.2, SJ11.3
unnamed: R52.2, SJ11.1
unnamed: R59.2, SJ10.1
unnamed: JP70.1, SJ12.1
unnamed: R61.2, U19.31
unnamed: C65.2, U19.28, Y4.3
unnamed: C64.2, U19.27, Y4.1
unnamed: R68.2, U21.12
unnamed: R69.2, U21.11
unnamed: Q10.1, R70.2
unnamed: Q11.1, R62.2
unnamed: IC4.1, IC4.2, R73.2
unnamed: IC4.5, R73.1, R74.2
unnamed: D17.C, R75.1
unnamed: D19.C, R77.2
unnamed: R77.1, U23.1
unnamed: R80.2, SJ14.2, U23.5
unnamed: D20.C, SJ13.2
unnamed: D20.A, R78.2
unnamed: R71.2, SJ15.3
unnamed: R72.2, SJ15.1
unnamed: R79.2, SJ14.1
unnamed: JP100.1, SJ16.1
unnamed: R81.2, U25.31
unnamed: C84.2, U25.28, Y5.3
unnamed: C83.2, U25.27, Y5.1
unnamed: R88.2, U27.12
unnamed: R89.2, U27.11
unnamed: Q13.1, R90.2
unnamed: Q14.1, R82.2
unnamed: IC5.1, IC5.2, R93.2
unnamed: IC5.5, R93.1, R94.2
unnamed: D22.C, R95.1
unnamed: D24.C, R97.2
unnamed: R97.1, U29.1
unnamed: R100.2, SJ18.2, U29.5
unnamed: D25.C, SJ17.2
unnamed: D25.A, R98.2
unnamed: R91.2, SJ19.3
unnamed: R92.2, SJ19.1
unnamed: R99.2, SJ18.1
unnamed: JP130.1, SJ20.1
unnamed: R101.2, U31.31
unnamed: C103.2, U31.28, Y6.3
unnamed: C102.2, U31.27, Y6.1
unnamed: R108.2, U33.12
unnamed: R109.2, U33.11
unnamed: Q16.1, R110.2
unnamed: Q17.1, R102.2
unnamed: IC6.1, IC6.2, R113.2
unnamed: IC6.5, R113.1, R114.2
unnamed: D27.C, R115.1
unnamed: D29.C, R117.2
unnamed: R117.1, U35.1
unnamed: R120.2, SJ22.2, U35.5
unnamed: D30.C, SJ21.2
unnamed: D30.A, R118.2
unnamed: R111.2, SJ23.3
unnamed: R112.2, SJ23.1
unnamed: R119.2, SJ22.1
unnamed: JP160.1, SJ24.1
unnamed: R121.2, U37.31
unnamed: C122.2, U37.28, Y7.3
unnamed: C121.2, U37.27, Y7.1
unnamed: R128.2, U39.12
unnamed: R129.2, U39.11
unnamed: Q19.1, R130.2
unnamed: Q20.1, R122.2
unnamed: IC7.1, IC7.2, R133.2
unnamed: IC7.5, R133.1, R134.2
unnamed: D32.C, R135.1
unnamed: D34.C, R137.2
unnamed: R137.1, U41.1
unnamed: R140.2, SJ26.2, U41.5
unnamed: D35.C, SJ25.2
unnamed: D35.A, R138.2
unnamed: R131.2, SJ27.3
unnamed: R132.2, SJ27.1
unnamed: R139.2, SJ26.1
unnamed: JP190.1, SJ28.1
unnamed: R141.2, U43.31
unnamed: C141.2, U43.28, Y8.3
unnamed: C140.2, U43.27, Y8.1
unnamed: R148.2, U45.12
unnamed: R149.2, U45.11
unnamed: Q22.1, R150.2
unnamed: Q23.1, R142.2
unnamed: IC8.1, IC8.2, R153.2
unnamed: IC8.5, R153.1, R154.2
unnamed: D37.C, R155.1
unnamed: D39.C, R157.2
unnamed: R157.1, U47.1
unnamed: R160.2, SJ30.2, U47.5
unnamed: D40.C, SJ29.2
unnamed: D40.A, R158.2
unnamed: R151.2, SJ31.3
unnamed: R152.2, SJ31.1
unnamed: R159.2, SJ30.1
unnamed: JP220.1, SJ32.1
unnamed: R161.2, U49.31
unnamed: C160.2, U49.28, Y9.3
unnamed: C159.2, U49.27, Y9.1
unnamed: R168.2, U51.12
unnamed: R169.2, U51.11
unnamed: Q25.1, R170.2
unnamed: Q26.1, R162.2
unnamed: IC9.1, IC9.2, R173.2
unnamed: IC9.5, R173.1, R174.2
unnamed: D42.C, R175.1
unnamed: D44.C, R177.2
unnamed: R177.1, U53.1
unnamed: R180.2, SJ34.2, U53.5
unnamed: D45.C, SJ33.2
unnamed: D45.A, R178.2
unnamed: R171.2, SJ35.3
unnamed: R172.2, SJ35.1
unnamed: R179.2, SJ34.1
unnamed: JP250.1, SJ36.1
unnamed: R181.2, U55.31
unnamed: C179.2, U55.28, Y10.3
unnamed: C178.2, U55.27, Y10.1
unnamed: R188.2, U57.12
unnamed: R189.2, U57.11
unnamed: Q28.1, R190.2
unnamed: Q29.1, R182.2
unnamed: IC10.1, IC10.2, R193.2
unnamed: IC10.5, R193.1, R194.2
unnamed: D47.C, R195.1
unnamed: D49.C, R197.2
unnamed: R197.1, U59.1
unnamed: R200.2, SJ38.2, U59.5
unnamed: D50.C, SJ37.2
unnamed: D50.A, R198.2
unnamed: R191.2, SJ39.3
unnamed: R192.2, SJ39.1
unnamed: R199.2, SJ38.1
unnamed: JP280.1, SJ40.1
unnamed: R201.2, U61.31
unnamed: C198.2, U61.28, Y11.3
unnamed: C197.2, U61.27, Y11.1
unnamed: R208.2, U63.12
unnamed: R209.2, U63.11
unnamed: Q31.1, R210.2
unnamed: Q32.1, R202.2
unnamed: IC11.1, IC11.2, R213.2
unnamed: IC11.5, R213.1, R214.2
unnamed: D52.C, R215.1
unnamed: D54.C, R217.2
unnamed: R217.1, U65.1
unnamed: R220.2, SJ42.2, U65.5
unnamed: D55.C, SJ41.2
unnamed: D55.A, R218.2
unnamed: R211.2, SJ43.3
unnamed: R212.2, SJ43.1
unnamed: R219.2, SJ42.1
unnamed: JP310.1, SJ44.1
unnamed: R221.2, U67.31
unnamed: C217.2, U67.28, Y12.3
unnamed: C216.2, U67.27, Y12.1
unnamed: R228.2, U69.12
unnamed: R229.2, U69.11
unnamed: Q34.1, R230.2
unnamed: Q35.1, R222.2
unnamed: IC12.1, IC12.2, R233.2
unnamed: IC12.5, R233.1, R234.2
unnamed: D57.C, R235.1
unnamed: D59.C, R237.2
unnamed: R237.1, U71.1
unnamed: R240.2, SJ46.2, U71.5
unnamed: D60.C, SJ45.2
unnamed: D60.A, R238.2
unnamed: R231.2, SJ47.3
unnamed: R232.2, SJ47.1
unnamed: R239.2, SJ46.1
unnamed: JP340.1, SJ48.1
unnamed: R241.2, U73.31
unnamed: C236.2, U73.28, Y13.3
unnamed: C235.2, U73.27, Y13.1
unnamed: R248.2, U75.12
unnamed: R249.2, U75.11
unnamed: Q37.1, R250.2
unnamed: Q38.1, R242.2
unnamed: IC13.1, IC13.2, R253.2
unnamed: IC13.5, R253.1, R254.2
unnamed: D62.C, R255.1
unnamed: D64.C, R257.2
unnamed: R257.1, U77.1
unnamed: R260.2, SJ50.2, U77.5
unnamed: D65.C, SJ49.2
unnamed: D65.A, R258.2
unnamed: R251.2, SJ51.3
unnamed: R252.2, SJ51.1
unnamed: R259.2, SJ50.1
unnamed: JP370.1, SJ52.1
unnamed: R261.2, U79.31
unnamed: C255.2, U79.28, Y14.3
unnamed: C254.2, U79.27, Y14.1
unnamed: R268.2, U81.12
unnamed: R269.2, U81.11
unnamed: Q40.1, R270.2
unnamed: Q41.1, R262.2
unnamed: IC14.1, IC14.2, R273.2
unnamed: IC14.5, R273.1, R274.2
unnamed: D67.C, R275.1
unnamed: D69.C, R277.2
unnamed: R277.1, U83.1
unnamed: R280.2, SJ54.2, U83.5
unnamed: D70.C, SJ53.2
unnamed: D70.A, R278.2
unnamed: R271.2, SJ55.3
unnamed: R272.2, SJ55.1
unnamed: R279.2, SJ54.1
unnamed: JP400.1, SJ56.1
unnamed: R281.2, U85.31
unnamed: C274.2, U85.28, Y15.3
unnamed: C273.2, U85.27, Y15.1
unnamed: R288.2, U87.12
unnamed: R289.2, U87.11
unnamed: Q43.1, R290.2
unnamed: Q44.1, R282.2
unnamed: IC15.1, IC15.2, R293.2
unnamed: IC15.5, R293.1, R294.2
unnamed: D72.C, R295.1
unnamed: D74.C, R297.2
unnamed: R297.1, U89.1
unnamed: R300.2, SJ58.2, U89.5
unnamed: D75.C, SJ57.2
unnamed: D75.A, R298.2
unnamed: R291.2, SJ59.3
unnamed: R292.2, SJ59.1
unnamed: R299.2, SJ58.1
unnamed: JP430.1, SJ60.1
RESET: JP28.1, Q2.3, R10.1, U2.32
RESET1: JP50.1, Q4.3, R27.1, U7.32
RESET2: JP80.1, Q7.3, R47.1, U13.32
RESET3: JP110.1, Q10.3, R67.1, U19.32
RESET4: JP140.1, Q13.3, R87.1, U25.32
RESET5: JP170.1, Q16.3, R107.1, U31.32
RESET6: JP200.1, Q19.3, R127.1, U37.32
RESET7: JP230.1, Q22.3, R147.1, U43.32
RESET8: JP260.1, Q25.3, R167.1, U49.32
RESET9: JP290.1, Q28.3, R187.1, U55.32
RESET10: JP320.1, Q31.3, R207.1, U61.32
RESET11: JP350.1, Q34.3, R227.1, U67.32
RESET12: JP380.1, Q37.3, R247.1, U73.32
RESET13: JP410.1, Q40.3, R267.1, U79.32
RESET14: JP440.1, Q43.3, R287.1, U85.32
RTS: Q2.2, R18.1, U4.2
RTS1: Q4.2, R22.1, U9.2
RTS2: Q7.2, R42.1, U15.2
RTS3: Q10.2, R62.1, U21.2
RTS4: Q13.2, R82.1, U27.2
RTS5: Q16.2, R102.1, U33.2
RTS6: Q19.2, R122.1, U39.2
RTS7: Q22.2, R142.1, U45.2
RTS8: Q25.2, R162.1, U51.2
RTS9: Q28.2, R182.1, U57.2
RTS10: Q31.2, R202.1, U63.2
RTS11: Q34.2, R222.1, U69.2
RTS12: Q37.2, R242.1, U75.2
RTS13: Q40.2, R262.1, U81.2
RTS14: Q43.2, R282.1, U87.2
SD_!HD!: U2.18, U5.7
SD_!HD!1: U7.18, U8.7
SD_!HD!2: U13.18, U14.7
SD_!HD!3: U19.18, U20.7
SD_!HD!4: U25.18, U26.7
SD_!HD!5: U31.18, U32.7
SD_!HD!6: U37.18, U38.7
SD_!HD!7: U43.18, U44.7
SD_!HD!8: U49.18, U50.7
SD_!HD!9: U55.18, U56.7
SD_!HD!10: U61.18, U62.7
SD_!HD!11: U67.18, U68.7
SD_!HD!12: U73.18, U74.7
SD_!HD!13: U79.18, U80.7
SD_!HD!14: U85.18, U86.7
SD_!WP!: U2.19, U5.3
SD_!WP!1: U7.19, U8.3
SD_!WP!2: U13.19, U14.3
SD_!WP!3: U19.19, U20.3
SD_!WP!4: U25.19, U26.3
SD_!WP!5: U31.19, U32.3
SD_!WP!6: U37.19, U38.3
SD_!WP!7: U43.19, U44.3
SD_!WP!8: U49.19, U50.3
SD_!WP!9: U55.19, U56.3
SD_!WP!10: U61.19, U62.3
SD_!WP!11: U67.19, U68.3
SD_!WP!12: U73.19, U74.3
SD_!WP!13: U79.19, U80.3
SD_!WP!14: U85.19, U86.3
SD_CLK: R9.1, U5.6
SD_CLK0: R9.2, U2.21
SD_CLK1: R26.1, U8.6
SD_CLK2: R26.2, U7.21
SD_CLK3: R46.1, U14.6
SD_CLK4: R46.2, U13.21
SD_CLK5: R66.1, U20.6
SD_CLK6: R66.2, U19.21
SD_CLK7: R86.1, U26.6
SD_CLK8: R86.2, U25.21
SD_CLK9: R106.1, U32.6
SD_CLK10: R106.2, U31.21
SD_CLK11: R126.1, U38.6
SD_CLK12: R126.2, U37.21
SD_CLK13: R146.1, U44.6
SD_CLK14: R146.2, U43.21
SD_CLK15: R166.1, U50.6
SD_CLK16: R166.2, U49.21
SD_CLK17: R186.1, U56.6
SD_CLK18: R186.2, U55.21
SD_CLK19: R206.1, U62.6
SD_CLK20: R206.2, U61.21
SD_CLK21: R226.1, U68.6
SD_CLK22: R226.2, U67.21
SD_CLK23: R246.1, U74.6
SD_CLK24: R246.2, U73.21
SD_CLK25: R266.1, U80.6
SD_CLK26: R266.2, U79.21
SD_CLK27: R286.1, U86.6
SD_CLK28: R286.2, U85.21
SD_CS0: U2.20, U5.1
SD_CS1: U7.20, U8.1
SD_CS2: U13.20, U14.1
SD_CS3: U19.20, U20.1
SD_CS4: U25.20, U26.1
SD_CS5: U31.20, U32.1
SD_CS6: U37.20, U38.1
SD_CS7: U43.20, U44.1
SD_CS8: U49.20, U50.1
SD_CS9: U55.20, U56.1
SD_CS10: U61.20, U62.1
SD_CS11: U67.20, U68.1
SD_CS12: U73.20, U74.1
SD_CS13: U79.20, U80.1
SD_CS14: U85.20, U86.1
SD_SI: U2.23, U5.5
SD_SI1: U7.23, U8.5
SD_SI2: U13.23, U14.5
SD_SI3: U19.23, U20.5
SD_SI4: U25.23, U26.5
SD_SI5: U31.23, U32.5
SD_SI6: U37.23, U38.5
SD_SI7: U43.23, U44.5
SD_SI8: U49.23, U50.5
SD_SI9: U55.23, U56.5
SD_SI10: U61.23, U62.5
SD_SI11: U67.23, U68.5
SD_SI12: U73.23, U74.5
SD_SI13: U79.23, U80.5
SD_SI14: U85.23, U86.5
SD_SO: U2.22, U5.2
SD_SO1: U7.22, U8.2
SD_SO2: U13.22, U14.2
SD_SO3: U19.22, U20.2
SD_SO4: U25.22, U26.2
SD_SO5: U31.22, U32.2
SD_SO6: U37.22, U38.2
SD_SO7: U43.22, U44.2
SD_SO8: U49.22, U50.2
SD_SO9: U55.22, U56.2
SD_SO10: U61.22, U62.2
SD_SO11: U67.22, U68.2
SD_SO12: U73.22, U74.2
SD_SO13: U79.22, U80.2
SD_SO14: U85.22, U86.2
SHIELD: JP15.SHIELD1, JP15.SHIELD2, JP15.SHIELD3
SHIELD1: JP31.SHIELD1, JP31.SHIELD2, JP31.SHIELD3
SHIELD2: JP61.SHIELD1, JP61.SHIELD2, JP61.SHIELD3
SHIELD3: JP91.SHIELD1, JP91.SHIELD2, JP91.SHIELD3
SHIELD4: JP121.SHIELD1, JP121.SHIELD2, JP121.SHIELD3
SHIELD5: JP151.SHIELD1, JP151.SHIELD2, JP151.SHIELD3
SHIELD6: JP181.SHIELD1, JP181.SHIELD2, JP181.SHIELD3
SHIELD7: JP211.SHIELD1, JP211.SHIELD2, JP211.SHIELD3
SHIELD8: JP241.SHIELD1, JP241.SHIELD2, JP241.SHIELD3
SHIELD9: JP271.SHIELD1, JP271.SHIELD2, JP271.SHIELD3
SHIELD10: JP301.SHIELD1, JP301.SHIELD2, JP301.SHIELD3
SHIELD11: JP331.SHIELD1, JP331.SHIELD2, JP331.SHIELD3
SHIELD12: JP361.SHIELD1, JP361.SHIELD2, JP361.SHIELD3
SHIELD13: JP391.SHIELD1, JP391.SHIELD2, JP391.SHIELD3
SHIELD14: JP421.SHIELD1, JP421.SHIELD2, JP421.SHIELD3
TRACE_ANT: C8.2, E1.ANT, L2.1
TRACE_ANT1: C28.2, E2.ANT, L4.1
TRACE_ANT2: C47.2, E3.ANT, L6.1
TRACE_ANT3: C66.2, E4.ANT, L8.1
TRACE_ANT4: C85.2, E5.ANT, L10.1
TRACE_ANT5: C104.2, E6.ANT, L12.1
TRACE_ANT6: C123.2, E7.ANT, L14.1
TRACE_ANT7: C142.2, E8.ANT, L16.1
TRACE_ANT8: C161.2, E9.ANT, L18.1
TRACE_ANT9: C180.2, E10.ANT, L20.1
TRACE_ANT10: C199.2, E11.ANT, L22.1
TRACE_ANT11: C218.2, E12.ANT, L24.1
TRACE_ANT12: C237.2, E13.ANT, L26.1
TRACE_ANT13: C256.2, E14.ANT, L28.1
TRACE_ANT14: C275.2, E15.ANT, L30.1
U0RXI: JP8.1@2, JP9.1, U2.25, U4.20
U0RXI1: JP53.1@2, JP54.1, U7.25, U9.20
U0RXI2: JP83.1@2, JP84.1, U13.25, U15.20
U0RXI3: JP113.1@2, JP114.1, U19.25, U21.20
U0RXI4: JP143.1@2, JP144.1, U25.25, U27.20
U0RXI5: JP173.1@2, JP174.1, U31.25, U33.20
U0RXI6: JP203.1@2, JP204.1, U37.25, U39.20
U0RXI7: JP233.1@2, JP234.1, U43.25, U45.20
U0RXI8: JP263.1@2, JP264.1, U49.25, U51.20
U0RXI9: JP293.1@2, JP294.1, U55.25, U57.20
U0RXI10: JP323.1@2, JP324.1, U61.25, U63.20
U0RXI11: JP353.1@2, JP354.1, U67.25, U69.20
U0RXI12: JP383.1@2, JP384.1, U73.25, U75.20
U0RXI13: JP413.1@2, JP414.1, U79.25, U81.20
U0RXI14: JP443.1@2, JP444.1, U85.25, U87.20
U0TXO: JP10.1@2, JP11.1, U2.26, U4.4
U0TXO1: JP51.1@2, JP52.1, U7.26, U9.4
U0TXO2: JP81.1@2, JP82.1, U13.26, U15.4
U0TXO3: JP111.1@2, JP112.1, U19.26, U21.4
U0TXO4: JP141.1@2, JP142.1, U25.26, U27.4
U0TXO5: JP171.1@2, JP172.1, U31.26, U33.4
U0TXO6: JP201.1@2, JP202.1, U37.26, U39.4
U0TXO7: JP231.1@2, JP232.1, U43.26, U45.4
U0TXO8: JP261.1@2, JP262.1, U49.26, U51.4
U0TXO9: JP291.1@2, JP292.1, U55.26, U57.4
U0TXO10: JP321.1@2, JP322.1, U61.26, U63.4
U0TXO11: JP351.1@2, JP352.1, U67.26, U69.4
U0TXO12: JP381.1@2, JP382.1, U73.26, U75.4
U0TXO13: JP411.1@2, JP412.1, U79.26, U81.4
U0TXO14: JP441.1@2, JP442.1, U85.26, U87.4
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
